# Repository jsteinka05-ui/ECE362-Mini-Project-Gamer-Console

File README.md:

# ECE 362 Mini Project — Cup Pong Game Console

## Project Overview

This project is a mini game console developed for **ECE 362: Microprocessor Systems and Interfacing** at Purdue University. Using the RP2350B microcontroller on the Purdue Proton development board, our team is building a top-down Cup Pong game that integrates multiple hardware peripherals.

The goal is to create an interactive game where players use a joystick to aim and throw a ball into a formation of cups displayed on an LCD screen. Successfully landing a ball in a cup removes it from the table, and the player attempts to clear all 10 cups in as few shots as possible.

The project incorporates SPI, ADC, PWM, and I2C communication to support graphics, player controls, audio feedback, and score storage.

## Hardware Components

| Component | Purpose | Interface |
|---|---|---|
| Purdue Proton (RP2350B) | Main microcontroller | — |
| 2.2" TFT LCD (ILI9341) | Game graphics and animations | SPI |
| Analog Joystick | Aiming and shooting controls | ADC / GPIO |
| Speaker | Game sound effects | PWM |
| EEPROM | High-score storage | I2C |

## Schematic and PCB

### Rev 1.2 schematic

### Rev 1.2 PCB

Top view of the bare carrier board.

## Team Responsibilities

| Team Member | Responsibility |
|---|---|
| Adi | SPI LCD initialization, display driver, and Cup Pong graphics |
| Brandon | ADC joystick input and controls |
| Raghav | PWM speaker and sound effects |
| Joey | I2C EEPROM and score storage, KiCad Schematic and PCB Creation |

Each peripheral is developed separately before being integrated into the complete game.

## Gameplay

Cup Pong uses a top-down view of a table with 10 cups arranged in a triangle.

1. The player moves the joystick to position an aiming crosshair.
2. Pressing the joystick button launches a ball toward the selected location.
3. If the ball lands inside an active cup, the cup is removed.
4. The number of remaining cups and total shots is displayed on the LCD.
5. The round ends when all 10 cups are cleared.
6. The player's best score, measured by the fewest shots, can be saved using EEPROM.

## Building the Project

### Requirements

- Visual Studio Code
- PlatformIO extension
- Purdue Proton development board
- Raspberry Pi Pico SDK (configured through PlatformIO)

### Instructions

1. Clone the repository:

   ```bash
   git clone https://github.com/jsteinka05-ui/ECE362-Mini-Project-Gamer-Console.git
   ```

2. Open the repository folder in VS Code.

3. Allow PlatformIO to install the necessary dependencies.

4. Select the `proton` environment and run **PlatformIO: Build**.

5. Once the hardware is connected, upload the firmware to the Proton using the configured upload/debug interface.

The PlatformIO build has been completed successfully. LCD hardware testing is still pending.

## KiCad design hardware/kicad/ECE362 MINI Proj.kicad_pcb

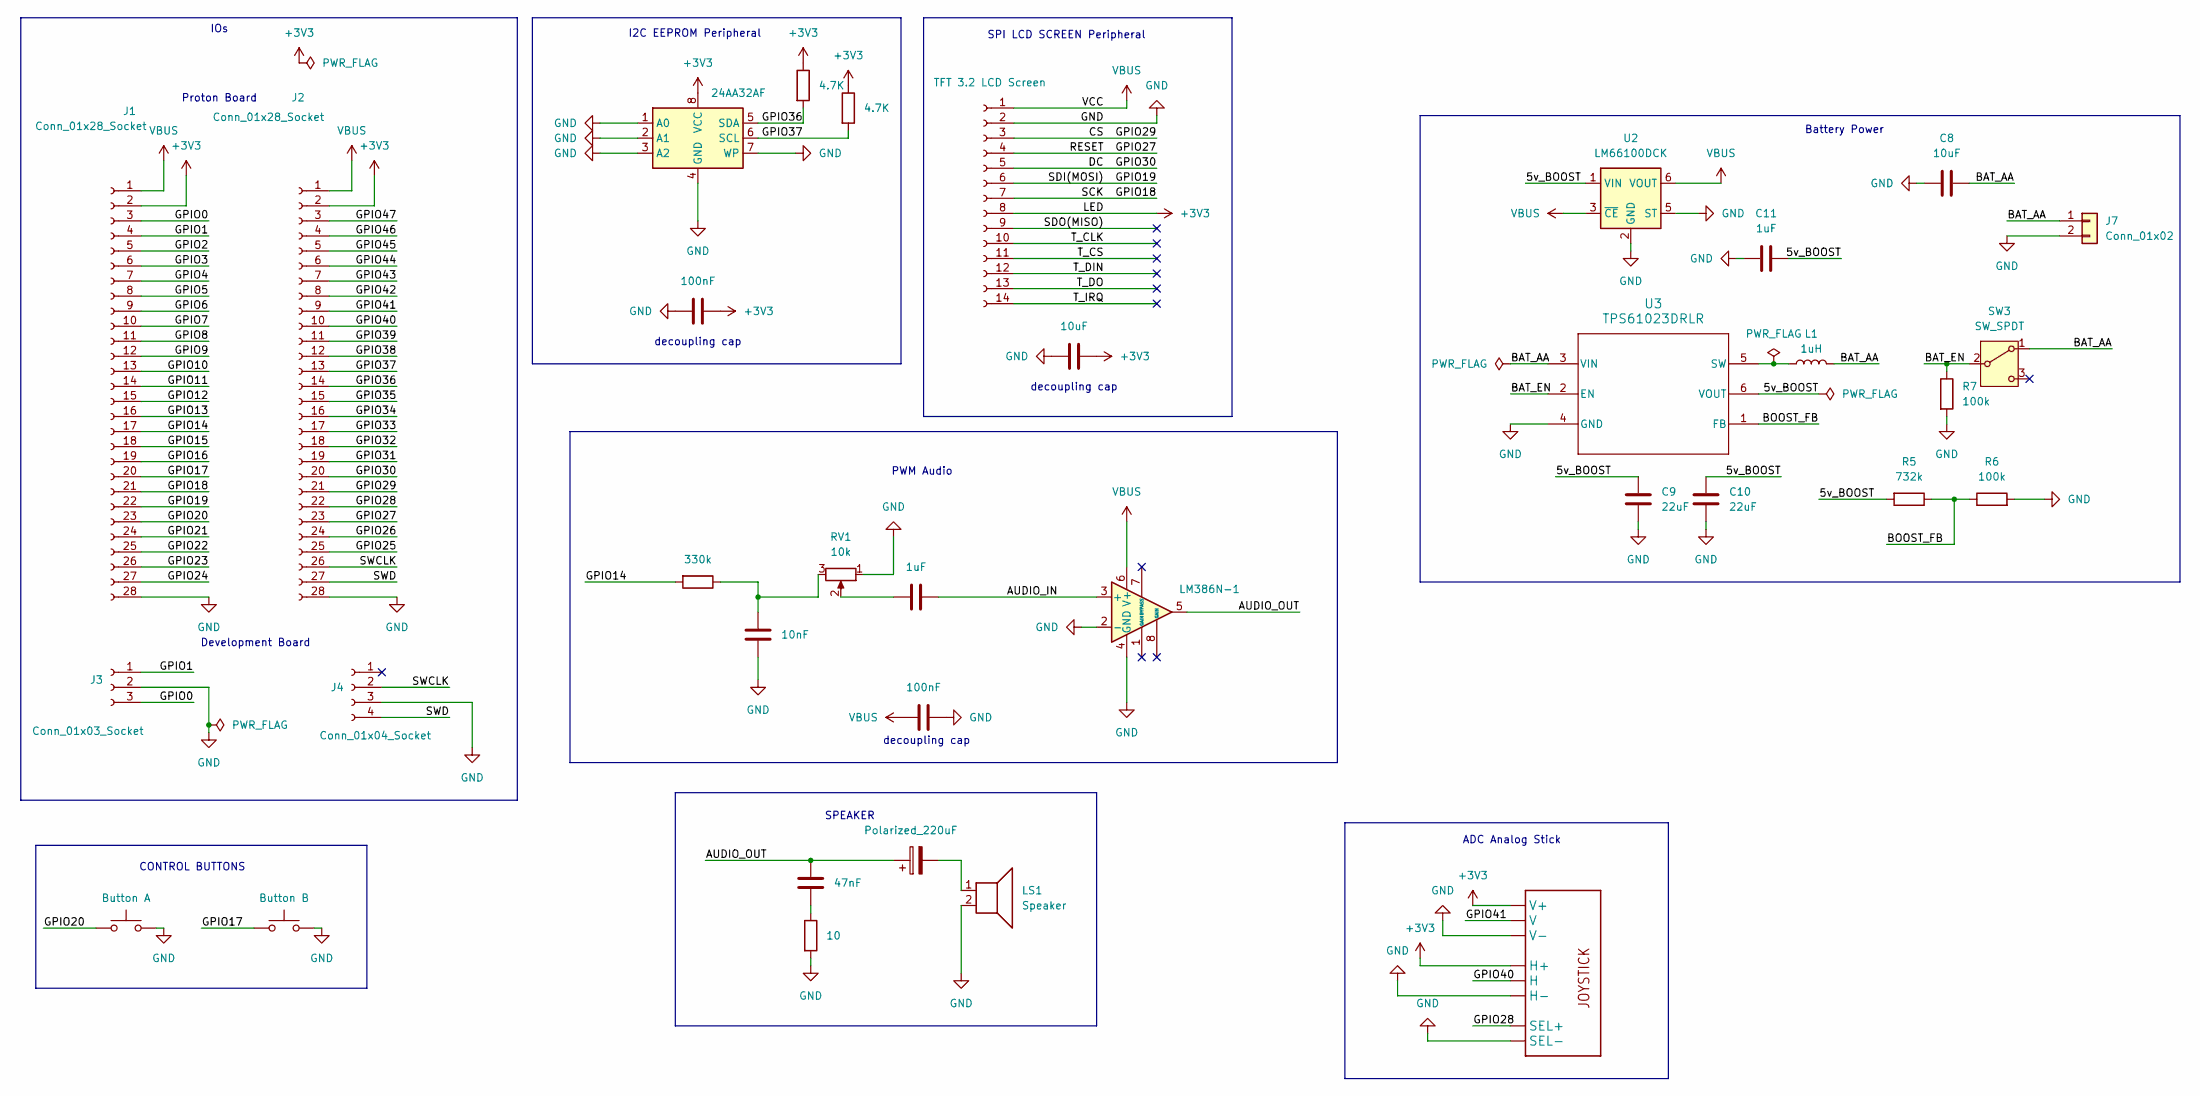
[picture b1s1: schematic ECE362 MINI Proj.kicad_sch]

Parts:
C1, C5: 100nF; C_0805_2012Metric; LCSC Part # C49678
C2, C8: 10uF; C_1206_3216Metric; LCSC Part # C13585
C3: 10nF; C_0805_2012Metric; LCSC Part # C1710
C4, C11: 1uF; C_0805_2012Metric; LCSC Part # C28323
C6: 47nF; C_0805_2012Metric; LCSC Part # C53134
C7: Polarized_220uF; CP_Elec_6.3x7.7; LCSC Part # C2827940
C9, C10: 22uF; C_1206_3216Metric; LCSC Part # C12891
J1, J2: Conn_01x28_Socket; PinSocket_1x28_P2.54mm_Vertical
J3: Conn_01x03_Socket; PinSocket_1x03_P2.54mm_Vertical
J4: Conn_01x04_Socket; PinSocket_1x04_P2.54mm_Vertical
J5: TFT 3.2 LCD Screen; PinSocket_1x14_P2.54mm_Vertical
J7: Conn_01x02; TerminalBlock_Phoenix_MKDS-1,5-2-5.08_1x02_P5.08mm_Horizont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
L1: 1uH; L_Sunlord_MWSA0402S; LCSC Part # C408332
LS1: Speaker; Speaker_Adafruit1898_D29.3_P15
R1, R2: 4.7K; R_0805_2012Metric; LCSC Part # C17673
R3: 330k; R_0805_2012Metric; LCSC Part # C17629
R4: 10; R_1206_3216Metric; LCSC Part # C17903
R5: 732k; R_0805_2012Metric; LCSC Part # C17816
R6, R7: 100k; R_0805_2012Metric; LCSC Part # C17407
RV1: 10k; Potentiometer_Adafruit4271
SW1: Button A; SW_SPST_Omron_B3F-40xx
SW2: Button B; SW_SPST_Omron_B3F-40xx
SW3: SW_SPDT; PinHeader_1x03_P2.54mm_Vertical
U1: LM386N-1; DIP-8_W7.62mm
U2: LM66100DCK; SOT-363_SC-70-6; LCSC Part # C2869734
U3: TPS61023DRLR; SOT-563; LCSC Part # C919459
U4: JOYSTICKPTH; JOYSTICK_ADAFRUIT512
U7: 24AA32AF; DIP-8_W7.62mm

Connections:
+3V3: C1.1, C2.1, J1.2, J2.2, J5.8, R1.1, R2.1, U4.H1 (H+), U4.V1 (V+), U7.8 (VCC)
/5v_BOOST: C9.1, C10.1, C11.2, R5.2, U2.1 (VIN), U3.6 (VOUT)
/AUDIO_IN: C4.2, U1.3 (+)
/AUDIO_OUT: C6.1, C7.1, U1.5
/BAT_AA: C8.2, J7.1, L1.2, SW3.1 (A), U3.3 (VIN)
/BAT_EN: R7.1, SW3.2 (B), U3.2 (EN)
/BOOST_FB: R5.1, R6.1, U3.1 (FB)
/CS: J2.21, J5.3
/DC: J2.20, J5.5
/GPIO0: J1.3, J3.3
/GPIO1: J1.4, J3.1
/GPIO2: J1.5
/GPIO3: J1.6
/GPIO4: J1.7
/GPIO5: J1.8
/GPIO6: J1.9
/GPIO7: J1.10
/GPIO8: J1.11
/GPIO9: J1.12
/GPIO10: J1.13
/GPIO11: J1.14
/GPIO12: J1.15
/GPIO13: J1.16
/GPIO14: J1.17, R3.2
/GPIO15: J1.18
/GPIO16: J1.19
/GPIO17: J1.20, SW2.1
/GPIO18: J1.21, J5.7
/GPIO19: J1.22, J5.6
/GPIO20: J1.23, SW1.1
/GPIO21: J1.24
/GPIO22: J1.25
/GPIO23: J1.26
/GPIO24: J1.27
/GPIO25: J2.25
/GPIO26: J2.24
/GPIO27: J2.23, J5.4
/GPIO28: J2.22, U4.B1A (SEL+)
/GPIO31: J2.19
/GPIO32: J2.18
/GPIO33: J2.17
/GPIO34: J2.16
/GPIO35: J2.15
/GPIO36: J2.14, R2.2, U7.5 (SDA)
/GPIO37: J2.13, R1.2, U7.6 (SCL)
/GPIO38: J2.12
/GPIO39: J2.11
/GPIO40: J2.10, U4.H2 (H)
/GPIO41: J2.9, U4.V2 (V)
/GPIO42: J2.8
/GPIO43: J2.7
/GPIO44: J2.6
/GPIO45: J2.5
/GPIO46: J2.4
/GPIO47: J2.3
/SDO(MISO): J5.9
/SWCLK: J2.26, J4.2
/SWD: J2.27, J4.4
/T_CLK: J5.10
/T_CS: J5.11
/T_DIN: J5.12
/T_DO: J5.13
/T_IRQ: J5.14
GND: C1.2, C2.2, C3.2, C5.2, C8.1, C9.2, C10.2, C11.1, J1.28, J2.28, J3.2, J4.3, J5.2, J7.2, LS1.2, R4.2, R6.2, R7.2, RV1.1, SW1.2, SW2.2, U1.2 (-), U1.4 (GND), U2.2 (GND), U2.5 (ST), U3.4 (GND), U4.B2A (SEL-), U4.H3 (H-), U4.V3 (V-), U7.1 (A0), U7.2 (A1), U7.3 (A2), U7.4 (GND), U7.7 (WP)
unnamed: C3.1, R3.1, RV1.3
unnamed: C4.1, RV1.2
unnamed: C6.2, R4.1
unnamed: C7.2, LS1.1
unnamed: L1.1, U3.5 (SW)
VBUS: C5.1, J1.1, J2.1, J5.1, U1.6 (V+), U2.3 (~CE), U2.6 (VOUT)

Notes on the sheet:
PWM Audio
SPEAKER
decoupling cap
IOs
SPI LCD SCREEN Peripheral
Battery Power
Proton Board
Development Board
I2C EEPROM Peripheral
CONTROL BUTTONS
ADC Analog Stick

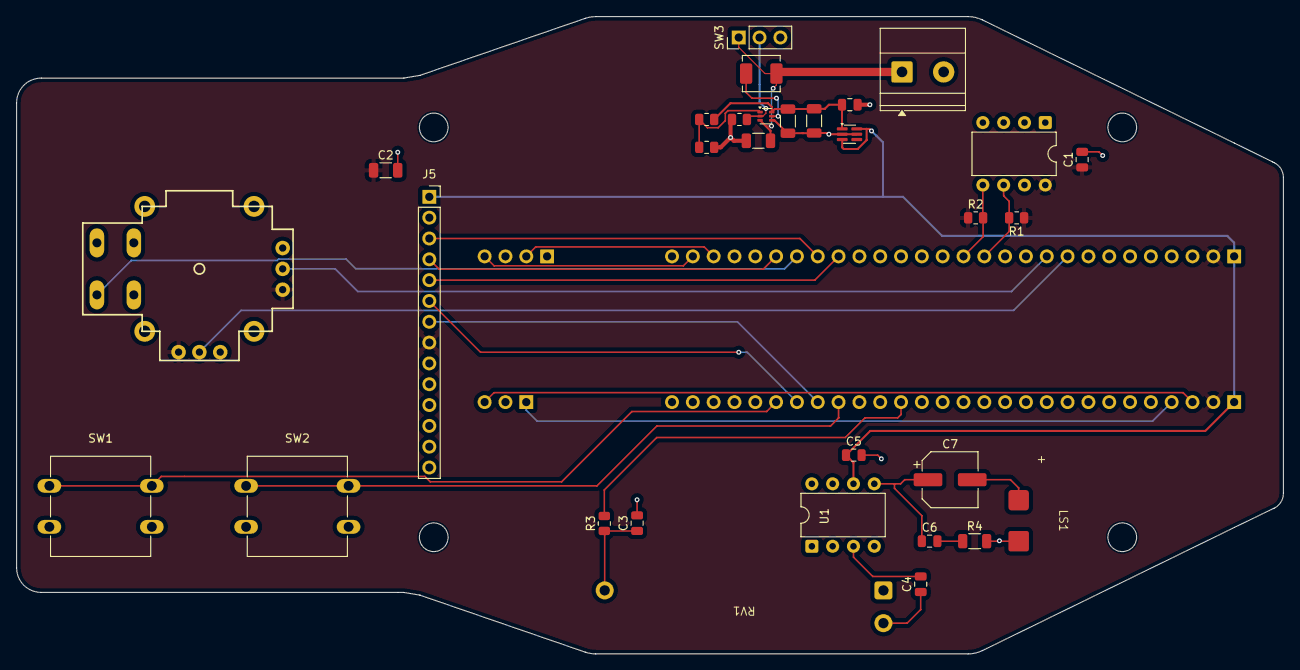
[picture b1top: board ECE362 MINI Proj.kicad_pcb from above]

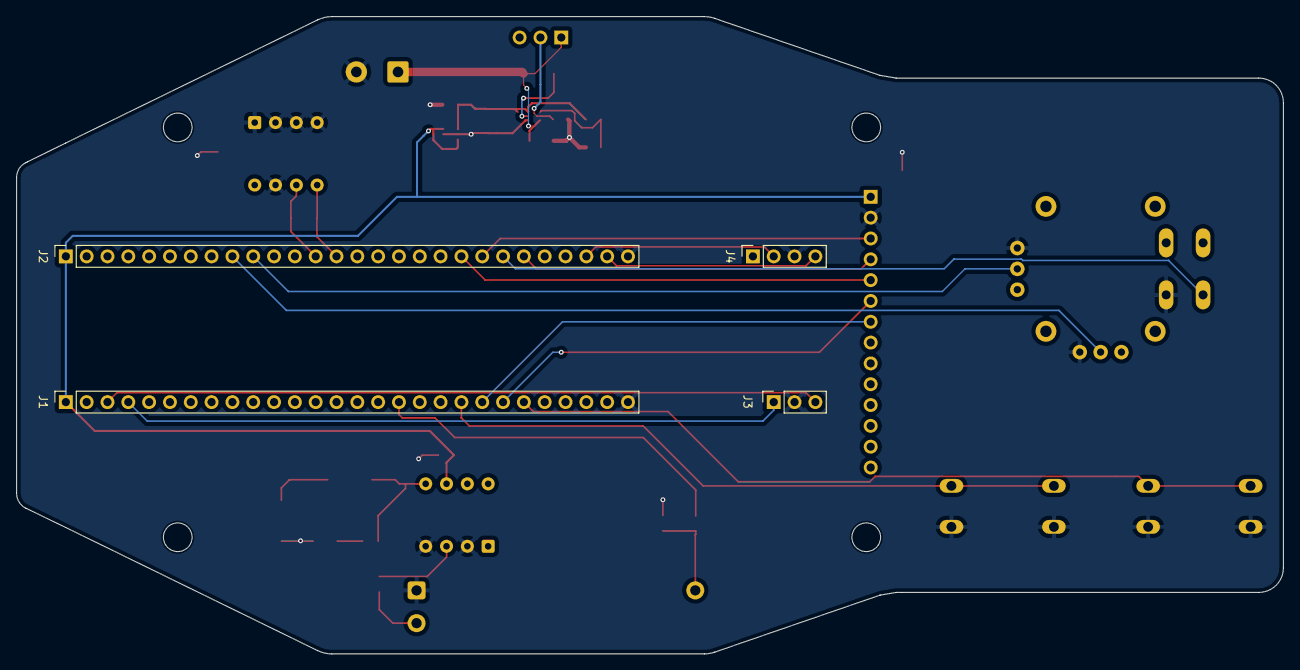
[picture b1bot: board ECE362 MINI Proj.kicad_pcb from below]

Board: 2 copper layers, 154.5 x 77.8 mm, 35 parts (4 on the bottom side), 31 nets.

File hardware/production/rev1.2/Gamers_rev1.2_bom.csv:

Designator,Footprint,Quantity,Value,LCSC Part #
"C1, C5",0805,2,100nF, C49678
"C10, C9",1206,2,22uF, C12891
"C11, C4",0805,2,1uF, C28323
"C2, C8",1206,2,10uF, C13585
C3,0805,1,10nF, C1710
C6,0805,1,47nF, C53134
C7,CP_Elec_6.3x7.7,1,Polarized_220uF, C2827940
L1,L_Sunlord_MWSA0402S,1,1uH, C408332
"R1, R2",0805,2,4.7K, C17673
R3,0805,1,330k, C17629
R4,1206,1,10, C17903
R5,0805,1,732k,C17816
"R6, R7",0805,2,100k, C17407
U2,SOT-363_SC-70-6,1,LM66100DCK, C2869734
U3,SOT-563,1,TPS61023DRLR,C919459
